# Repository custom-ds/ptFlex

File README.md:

# ptFlex
ptFlex tracker board starting with version 2.0 of the hardware, which is based on the improvements found in the ptSolar tracker. This repo supercedes the original ptFlex-firmware and ptFlex-Hardware repos from the version 1.0 hardware.

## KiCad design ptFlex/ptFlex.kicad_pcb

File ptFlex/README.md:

# ptFlex PCB
The ptFlex PCB has been designed for manufacture from JLC-PCB. The design rules checker have been tuned for their manufacturing tolerances.

The design and update process includes updating the Schematic in KiCad, updating the PCB layout based on the schematic changes in KiCad, then output the Gerber files and assembly documents for upload to JLC-PCB.

## Schematic Design
Any changes to the schematic should be completed first. When placing a part, be sure to update the Bill of Materials information by including the following two Fields in each component's properties.

* **Digikey** - The Digikey part number for ordering parts (critical for any parts that are not auto-assembled by JLC), and import for all other parts in the event that someone would want to hand-assemble their tracker.
* **LCSC** - The JLC-PCB Part number for automated assembly. This value is not populated for through-hole parts and the SA818V transmitter module (sources from Alibaba, etc)

### Schematic Outputs

#### Bill of Materials
Once complete with the Schematic, run the Tools &rarr; Generate Bill of Materials which places the BOM inside of the /Current folder.

#### PDF Output
Run File &rarr; Plot and output a PDF version of the schematics into the /Current folder. Be sure to rename this output to ```schematic.pdf``` in the output directory before plotting the PCB design.

## PCB Design
Inside of the Schematic editor, press F8 to update the PCB layout with any changes to the schematic. Adjust any layouts as necessary.

### Design Rule Checker
Once a layout has been laid out, run the DRC to check for problems with the board. The castelated edges normally throw a dozen or more errors. Also, there are some silkscreen issues with the coax connector at the top of the board. Any other errors should be investigated and resolved.

### Update the PCB Version
Update the Silkscreen text that indicates the version of the PCB.

### PCB Outputs

#### Drill Files
Run the Files &rarr; Fabrication Outputs &rarr; Gerber. From that screen, click the Generate Drill Files and output the .DRL files into the /Current folder. The format should be Excellon, and the units Millimeters.

#### Gerbers
Close out of the Drill files window, and click the File &rarr; Fabrication &rarr; Plot button to generate the set of Gerber files. These should also go into the /Current folder.

#### Position Files
Run File &rarr; Fabrication Outputs &rarr; Component Placement Files. Select CSV for the Format, then click Generate Position File.

In the /Current folder, find the newly created ptFlex-top-pos.csv file and open it with a text editor. The very first header line needs to be replaced with this line to align with JLC's naming scheme.

```
Designator,Val,Package,Mid X,Mid Y,Rotation,Layer
```

#### PDF Output
Run File &rarr; Plot and output a PDF version of the pcb into the /Current folder. Select options for Black & White, and to plot as a single .PDF document. Be sure to rename this output to ```pcb.pdf``` in the output directory.

## Ordering the PCBs
### Collecting the Output
Inside of the /Current directory, Zip up all of the files except the *.pdf and *.csv files. Name this .Zip file ptFlex-vX.X.X.zip, as appropriate for the board version.

## Upload to JLCPCB

Log in to your JLC-PCB account at [JLCPCB.com](https://www.jlcpcb.com/).

Upload the Gerbers to the site. For the ptFlex tracker, select the following options:
* Layers: 2
* PCB Qty: As desired
* Surface Finish: HASL (with lead)
* PCB Thickness: 1.6mm
* Castellated Holes: No
* PCB Assembly: As desired

### PCB Assembly
If PCB Assembly is desired:

* Assembly Side: Top Side 
* PCBA Qty: Select the quantity, up to the number of PCBs you selected in the first part

Select Next, then Next again.

Upload the following files:
* Add BOM: Upload the Bill of Materials.csv file.
* Add CPL: Upload the ptFlex-top-pos.csv file. Make sure that you modified the first header line as described above.

Process BOM & CPL. You will likely get an Error that certain Designators don't exist in the CPL file. That's just a warning that some parts that are located on the back of the board (SA818V and the Supercap) aren't found in the placement file. Click the Continue button if you receive this error.

Review the Bill of Materials and ensure that the part description matches the expected values. If certain parts aren't in-stock, you will either have to order them, or hand-place them once the semi-finished boards arrive.

Once the board layout appears with the components placed on it, you will need to review each of the placements of the parts. Many of the semiconductors will be rotated 90 of 180 degrees out of spec, and you will need to adjust them. The best optoin is to open the ptFlex-top-pos.csv file, and edit the rotation values inside of the file. By doing this, you will save the copy of rotations locally and re-ordering will be that much simpler and safer.

The column in question is the second-to-last field where most of the default values are 0.00000 or 180.00000.

For the ptFlex the following parts need to be tweaked in the X/Y position to fit the pads correctly:
* U1 (5V Regulator)
* J1 (Power Connector)

The following components need to be rotated:
* Q1-Q5 (transistors) - 180 degrees
* U2 (3.3V Regulator) - 90 degrees
* U3 (ATMega) - -90 degrees
* U4 (GPS) - -90 degrees
* U6 (BME280) - 90 degrees

## Create an Final Output Directory
Copy the entire contents of the /Current folder into a folder named for the PCB version. For example, /v2.0.0/ for safe keeping.

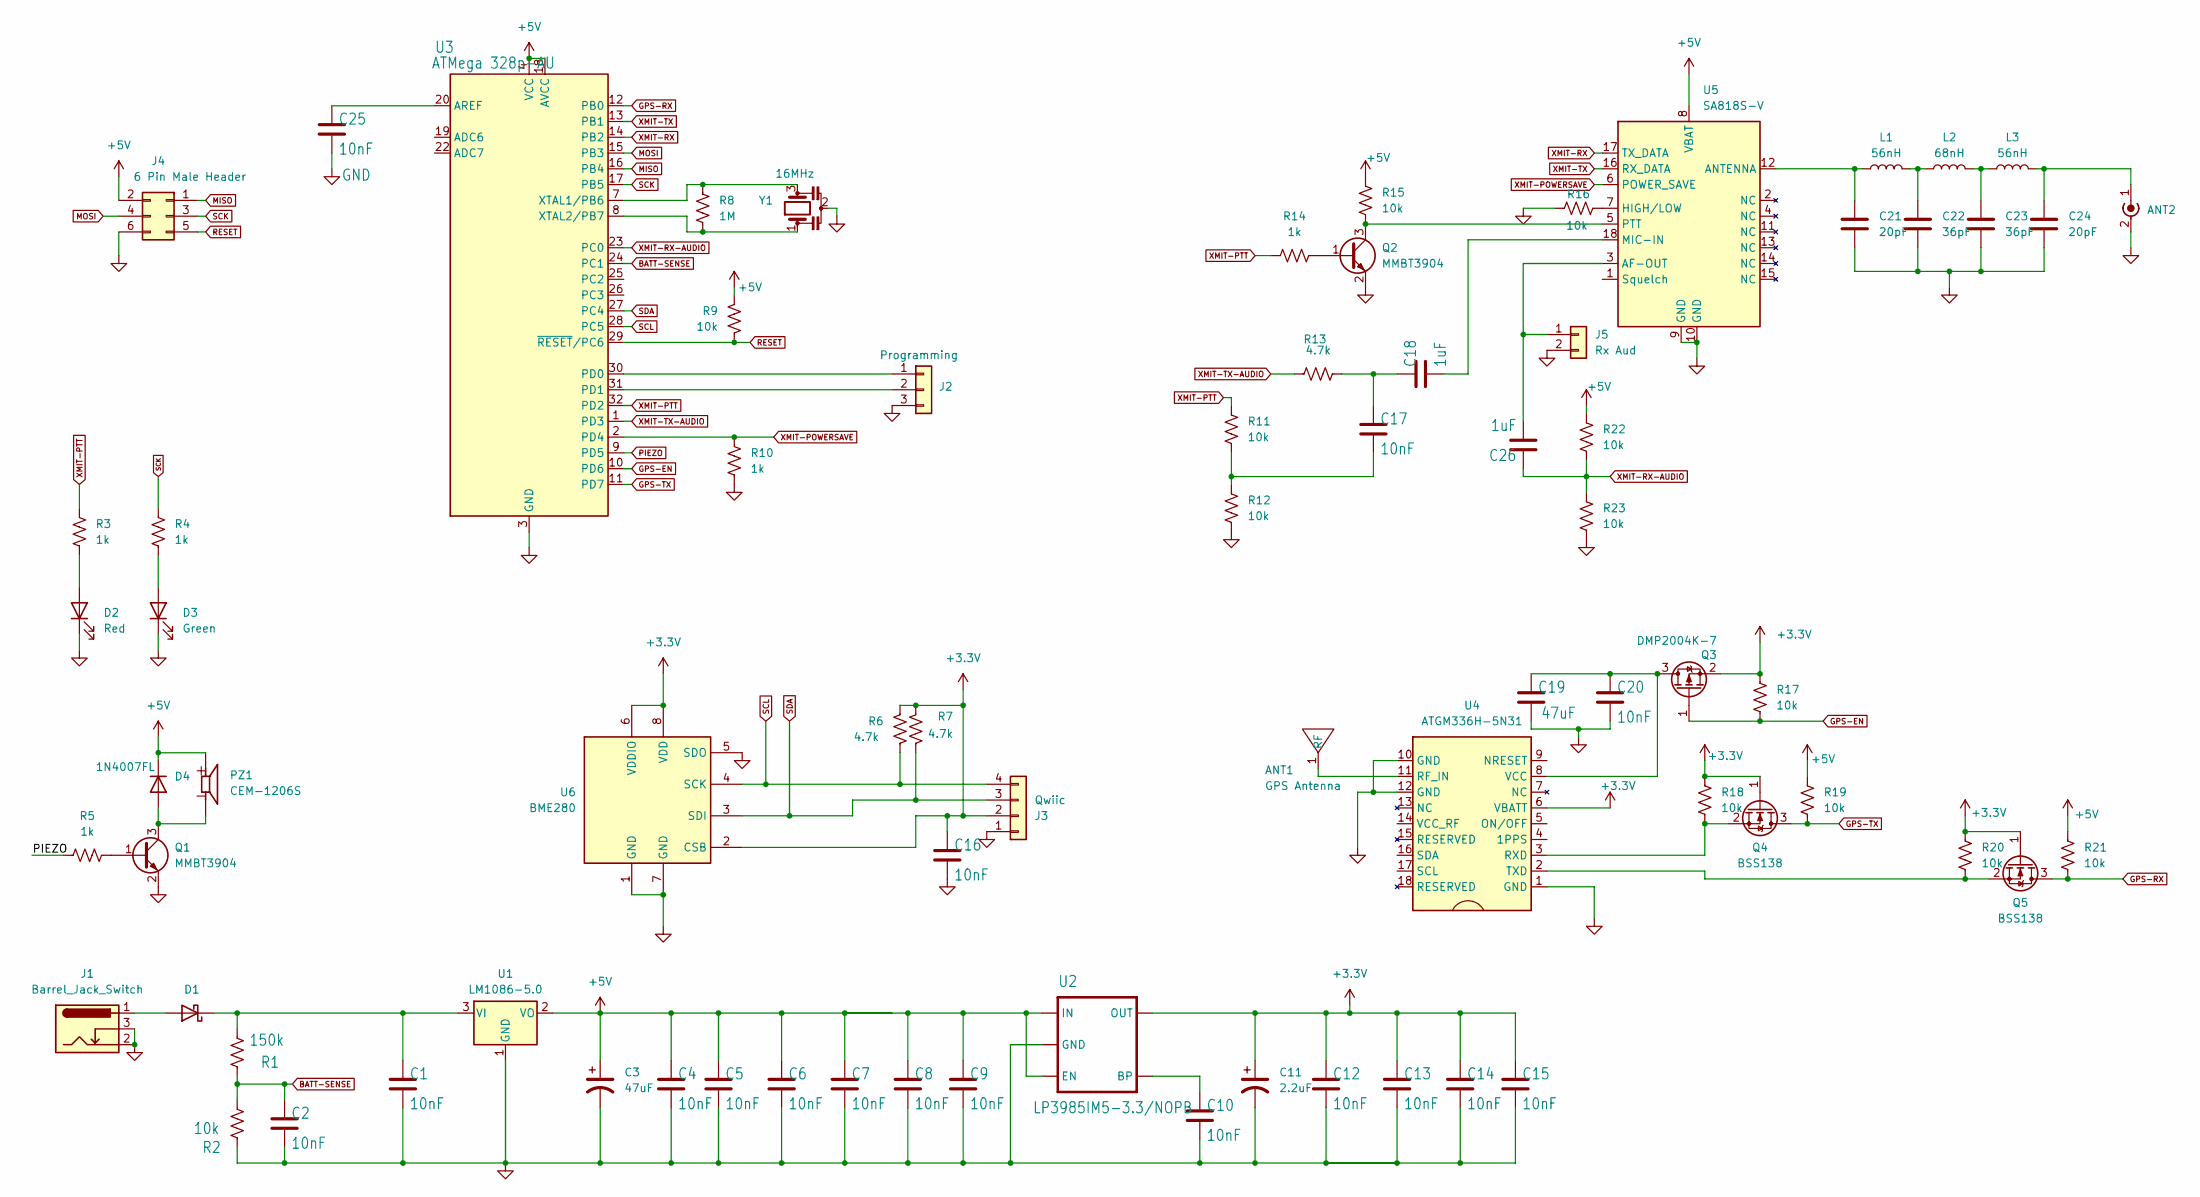
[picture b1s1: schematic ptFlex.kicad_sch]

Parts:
ANT1: GPS Antenna; Pulse ANT8010LL05R1575A Antenna; Digikey 553-ANT8010LL05R1575ACT-ND
ANT2: SMA Connector; SMA_Thru_Hole
C1, C2, C4, C5, C6, C7, C8, C9, C10, C12, C13, C14, C15, C16, C17, C20, C25: 10nF; C_0805_2012Metric; Digikey 399-1158-1-ND
C3, C19: 47uF; C_0805_2012Metric; Digikey 399-C0805C476M9PACTUCT-ND
C11: 2.2uF; C_0805_2012Metric; Digikey 445-1420-1-ND
C18, C26: 1uF; C_0805_2012Metric; Digikey 311-1886-1-ND
C21, C24: 20pF; C_0805_2012Metric; Digikey 712-1381-1-ND
C22, C23: 36pF; C_0805_2012Metric; Digikey 478-10473-1-ND
D1: CDBA340L-G Schottky; D_SMA; Digikey 641-1258-1-ND
D2: Red; D_0805_2012Metric; Digikey LTST-C171KRKT
D3: Green; D_0805_2012Metric; Digikey LTST-C171GKT
D4: 1N4007FL; D_SOD-123; Digikey 1655-1N4007FLCT-ND
J1: Barrel_Jack_Switch; BarrelJack_CLIFF_FC681465S_SMT_Horizontal; Digikey CP-002AHPJCT-ND
J2: Programming; PinHeader_1x03_P2.54mm_Vertical; Digikey 732-5316-ND
J3: Qwiic; JST_SH_SM04B-SRSS-TB_1x04-1MP_P1.00mm_Horizontal; Digikey 455-1804-1-ND
J4: 6 Pin Male Header; PinHeader_2x03_P2.54mm_Vertical; Digikey 732-5394-ND
J5: Rx Aud; PinHeader_1x02_P2.54mm_Vertical
L1, L3: 56nH; L_0805_2012Metric; Digikey 535-11570-1-ND
L2: 68nH; L_0805_2012Metric; Digikey 535-11572-1-ND
PZ1: CEM-1206S; CUI_CEM-1206S
Q1, Q2: MMBT3904; SOT-23; Digikey MMBT3904TPMSCT-ND
Q3: DMP2004K-7; SOT-23; Digikey DMP2004KDICT-ND
Q4, Q5: BSS138; SOT-23; Digikey BSS138TR-ND
R1: 150k; R_0805_2012Metric; Digikey 311-150KCRCT-ND
R2, R9, R11, R12, R15, R16, R17, R18, R19, R20, R21, R22, R23: 10k; R_0805_2012Metric; Digikey 13-RT0805FRD0710KLCT-ND
R3, R4, R5, R10, R14: 1k; R_0805_2012Metric; Digikey 311-1.0KARCT-ND
R6, R7, R13: 4.7k; R_0805_2012Metric; Digikey 311-4.7KARCT-ND
R8: 1M; R_0805_2012Metric; Digikey 311-1.0MARCT-ND
U1: LM1086-5.0; TO-263-3_TabPin2; Digikey LM1086ISX-5.0/NOPBCT-ND
U2: LP3985IM5-3.3/NOPB; SOT-23-5; Digikey LP3985IM5-3.3/NOPBCT-ND
U3: ATMega 328p-AU; TQFP-32_7x7mm_P0.8mm; Digikey ATMEGA328P-AU-ND
U4: ATGM336H-5N31; Digikey ALIEXPRESS
U5: SA818S-V; DRA818 SA818; Digikey ALIEXPRESS
U6: BME280; Bosch_LGA-8_2.5x2.5mm_P0.65mm_ClockwisePinNumbering; Digikey 828-1063-1-ND
Y1: 16MHz; Resonator_SMD_Murata_CSTxExxV-3Pin_3.0x1.1mm; Digikey 490-17948-2-ND

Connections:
+3.3V: C11.1, C12.1, C13.1, C14.1, C15.1, C16.1, J3.2, Q3.2 (S), Q4.1 (G), Q5.1 (G), R6.1, R7.1, R17.1, R18.2, R20.2, U2.5 (OUT), U4.6 (VBATT), U6.2 (CSB), U6.6 (VDDIO), U6.8 (VDD)
+5V: C3.1, C4.1, C5.1, C6.1, C7.1, C8.1, C9.1, D4.1 (K), J4.2, PZ1.P, R9.1, R15.2, R19.2, R21.2, R22.2, U1.2 (VO), U2.1 (IN), U2.3 (EN), U3.4 (VCC), U3.6 (VCC), U3.18 (AVCC), U5.8 (VBAT)
BATT-SENSE: C2.1, R1.1, R2.2, U3.24 (PC1)
GND: ANT2.2 (Ext), C1.2, C2.2, C3.2, C4.2, C5.2, C6.2, C7.2, C8.2, C9.2, C10.2, C11.2, C12.2, C13.2, C14.2, C15.2, C16.2, C19.2, C20.2, C21.1, C22.1, C23.1, C24.1, C25.2, D2.1 (K), D3.1 (K), J1.2, J1.3, J2.3, J3.1, J4.6, J5.2, Q1.2 (E), Q2.2 (E), R2.1, R10.1, R12.1, R16.1, R23.1, U1.1 (GND), U2.2 (GND), U3.3 (GND), U3.5 (GND), U3.21 (GND), U4.1 (GND), U4.10 (GND), U4.12 (GND), U5.9 (GND), U5.10 (GND), U6.1 (GND), U6.5 (SDO), U6.7 (GND), Y1.2
GPS-EN: Q3.1 (G), R17.2, U3.10 (PD6)
GPS-RX: Q5.3 (D), R21.1, U3.12 (PB0)
GPS-TX: Q4.3 (D), R19.1, U3.11 (PD7)
MISO: J4.1, U3.16 (PB4)
MOSI: J4.4, U3.15 (PB3)
unnamed: ANT1.1 (RF), U4.11 (RF_IN)
unnamed: ANT2.1 (In), C24.2, L3.2
unnamed: C17.1, C18.1, R13.2
unnamed: C17.2, R11.1, R12.2
unnamed: C22.2, L1.2, L2.1
unnamed: C23.2, L2.2, L3.1
unnamed: D1.2 (A), J1.1
unnamed: C1.1, D1.1 (K), R1.2, U1.3 (VI)
unnamed: D2.2 (A), R3.2
unnamed: D3.2 (A), R4.2
unnamed: D4.2 (A), PZ1.N, Q1.3 (C)
unnamed: J2.1, U3.30 (PD0)
unnamed: J2.2, U3.31 (PD1)
unnamed: C26.2, J5.1, U5.3 (AF-OUT)
unnamed: Q1.1 (B), R5.1
unnamed: Q2.1 (B), R14.2
unnamed: Q2.3 (C), R15.1, U5.5 (PTT)
unnamed: C19.1, C20.1, Q3.3 (D), U4.8 (VCC)
unnamed: Q4.2 (S), R18.1, U4.3 (RXD)
unnamed: Q5.2 (S), R20.1, U4.2 (TXD)
unnamed: C10.1, U2.4 (BP)
unnamed: C25.1, U3.20 (AREF)
unnamed: R8.1, U3.7 (XTAL1/PB6), Y1.3
unnamed: R8.2, U3.8 (XTAL2/PB7), Y1.1
unnamed: C21.2, L1.1, U5.12 (ANTENNA)
unnamed: R16.2, U5.7 (HIGH/LOW)
unnamed: C18.2, U5.18 (MIC-IN)
PIEZO: R5.2, U3.9 (PD5)
RESET: J4.5, R9.2, U3.29 (~RESET/PC6)
SCK: J4.3, R4.1, U3.17 (PB5)
SCL: J3.4, R6.2, U3.28 (PC5), U6.4 (SCK)
SDA: J3.3, R7.2, U3.27 (PC4), U6.3 (SDI)
XMIT-POWERSAVE: R10.2, U3.2 (PD4), U5.6 (POWER_SAVE)
XMIT-PTT: R3.1, R11.2, R14.1, U3.32 (PD2)
XMIT-RX: U3.14 (PB2), U5.17 (TX_DATA)
XMIT-RX-AUDIO: C26.1, R22.1, R23.2, U3.23 (PC0)
XMIT-TX: U3.13 (PB1), U5.16 (RX_DATA)
XMIT-TX-AUDIO: R13.1, U3.1 (PD3)

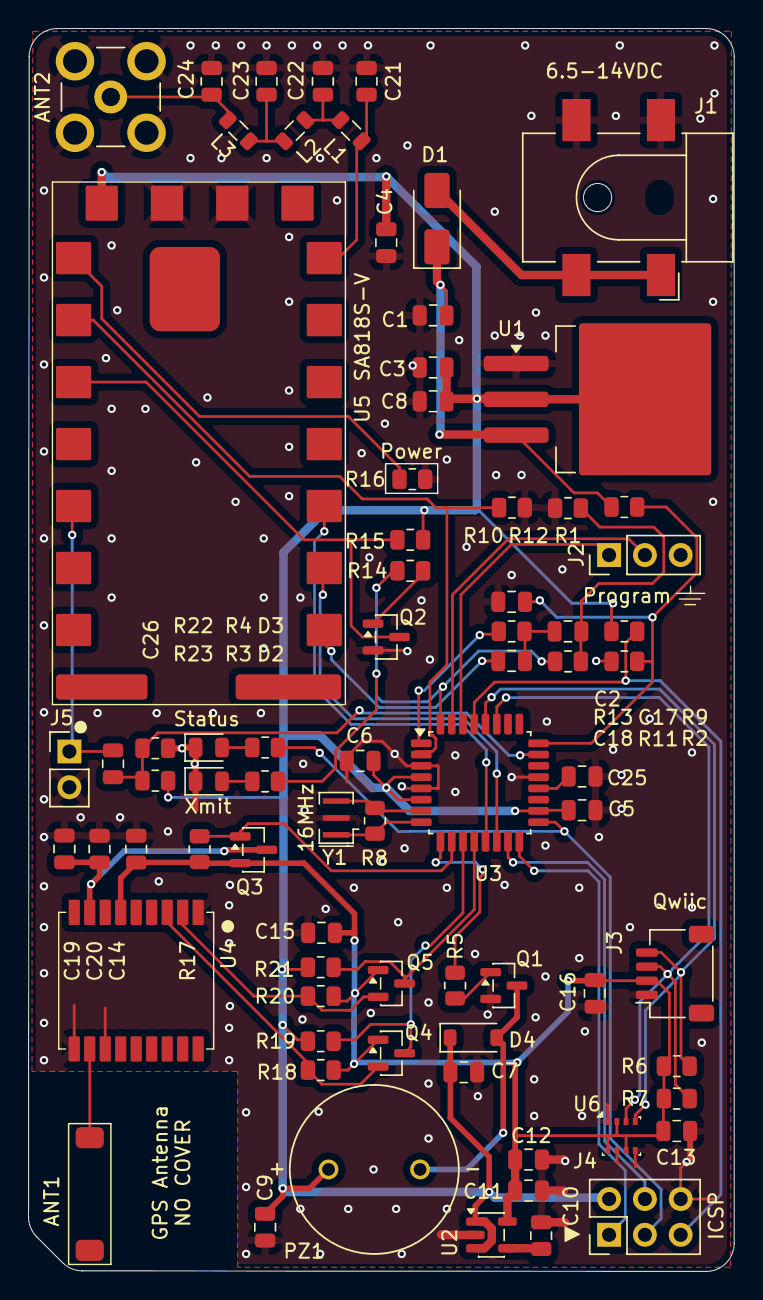
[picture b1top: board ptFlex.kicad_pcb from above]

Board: 2 copper layers, 50.1 x 88.2 mm, 76 parts (0 on the bottom side), 47 nets.

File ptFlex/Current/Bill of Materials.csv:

"Reference","Value","Datasheet","Footprint","Qty","DNP","Digikey","LCSC"
"ANT1","GPS Antenna","","Custom DS:Pulse ANT8010LL05R1575A Antenna","1","","553-ANT8010LL05R1575ACT-ND","C3284202"
"ANT2","SMA Connector","~","Custom DS:SMA_Thru_Hole","1","","",""
"C1,C2,C4,C5,C6,C7,C8,C9,C10,C12,C13,C14,C15,C16,C17,C20,C25","10nF","~","Capacitor_SMD:C_0805_2012Metric","17","","399-1158-1-ND","C83170"
"C3,C19","47uF","~","Capacitor_SMD:C_0805_2012Metric","2","","399-C0805C476M9PACTUCT-ND","C16780"
"C11","2.2uF","~","Capacitor_SMD:C_0805_2012Metric","1","","445-1420-1-ND","C107128"
"C18","1uF","~","Capacitor_SMD:C_0805_2012Metric","1","","311-1886-1-ND","C28323"
"C21,C24","20pF","~","Capacitor_SMD:C_0805_2012Metric","2","","712-1381-1-ND","C105173"
"C22,C23","36pF","~","Capacitor_SMD:C_0805_2012Metric","2","","478-10473-1-ND","C541518"
"D1","CDBA340L-G Schottky","~","Diode_SMD:D_SMA","1","","641-1258-1-ND","C22364900"
"D2","Red","~","Diode_SMD:D_0805_2012Metric","1","","LTST-C171KRKT","C2295"
"D3","Green","~","Diode_SMD:D_0805_2012Metric","1","","LTST-C171GKT","C2297 "
"D4","1N4007FL","","Diode_SMD:D_SOD-123","1","","1655-1N4007FLCT-ND","C7528871"
"J1","Barrel_Jack_Switch","~","Connector_BarrelJack:BarrelJack_CLIFF_FC681465S_SMT_Horizontal","1","","CP-002AHPJCT-ND ","C22434687"
"J2","Programming","~","Connector_PinHeader_2.54mm:PinHeader_1x03_P2.54mm_Vertical","1","","732-5316-ND",""
"J3","Qwiic","~","Connector_JST:JST_SH_SM04B-SRSS-TB_1x04-1MP_P1.00mm_Horizontal","1","","455-1804-1-ND","C160404"
"J4","6 Pin Male Header","~","Connector_PinHeader_2.54mm:PinHeader_2x03_P2.54mm_Vertical","1","","732-5394-ND",""
"L1,L3","56nH","~","Inductor_SMD:L_0805_2012Metric","2","","535-11570-1-ND","C98996"
"L2","68nH","~","Inductor_SMD:L_0805_2012Metric","1","","535-11572-1-ND","C75652"
"PZ1","CEM-1206S","","Custom DS:CUI_CEM-1206S","1","","",""
"Q1,Q2","MMBT3904","https://www.onsemi.com/pdf/datasheet/pzt3904-d.pdf","Package_TO_SOT_SMD:SOT-23","2","","MMBT3904TPMSCT-ND","C81464"
"Q3","DMP2004K-7","","Package_TO_SOT_SMD:SOT-23","1","","DMP2004KDICT-ND","C332297"
"Q4,Q5","BSS138","https://www.onsemi.com/pub/Collateral/BSS138-D.PDF","Package_TO_SOT_SMD:SOT-23","2","","BSS138TR-ND","C40912 "
"R1","150k","~","Resistor_SMD:R_0805_2012Metric","1","","311-150KCRCT-ND","C114558"
"R2,R9,R11,R12,R15,R16,R17,R18,R19,R20,R21","10k","~","Resistor_SMD:R_0805_2012Metric","11","","13-RT0805FRD0710KLCT-ND","C100047"
"R3,R4,R5,R10,R14","1k","~","Resistor_SMD:R_0805_2012Metric","5","","311-1.0KARCT-ND","C95781"
"R6,R7,R13","4.7k","~","Resistor_SMD:R_0805_2012Metric","3","","311-4.7KARCT-ND","C60816"
"R8","1M","~","Resistor_SMD:R_0805_2012Metric","1","","311-1.0MARCT-ND","C107700"
"U1","LM1086-5.0","","Package_TO_SOT_SMD:TO-263-3_TabPin2","1","","LM1086ISX-5.0/NOPBCT-ND","C5145331"
"U2","LP3985IM5-3.3/NOPB","https://www.ti.com/lit/ds/symlink/lp3985.pdf?HQS=dis-dk-null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","Package_TO_SOT_SMD:SOT-23-5","1","","LP3985IM5-3.3/NOPBCT-ND","C108877"
"U3","ATMega 328p-AU","https://ww1.microchip.com/downloads/en/DeviceDoc/Atmel-7810-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","Package_QFP:TQFP-32_7x7mm_P0.8mm","1","","ATMEGA328P-AU-ND","C14877"
"U4","ATGM336H-5N31","https://www.tinytronics.nl/product_files/002176_ATGM336H.pdf","Custom DS:ATGM336H-5N31","1","","ALIEXPRESS","C90770"
"U5","SA818S-V","","Custom DS:DRA818 SA818","1","","ALIEXPRESS",""
"U6","BME280","https://www.bosch-sensortec.com/media/boschsensortec/downloa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","Package_LGA:Bosch_LGA-8_2.5x2.5mm_P0.65mm_ClockwisePinNumbering","1","","828-1063-1-ND","C92489"
"Y1","16MHz","~","Crystal:Resonator_SMD_Murata_CSTxExxV-3Pin_3.0x1.1mm","1","","490-17948-2-ND","C341521"

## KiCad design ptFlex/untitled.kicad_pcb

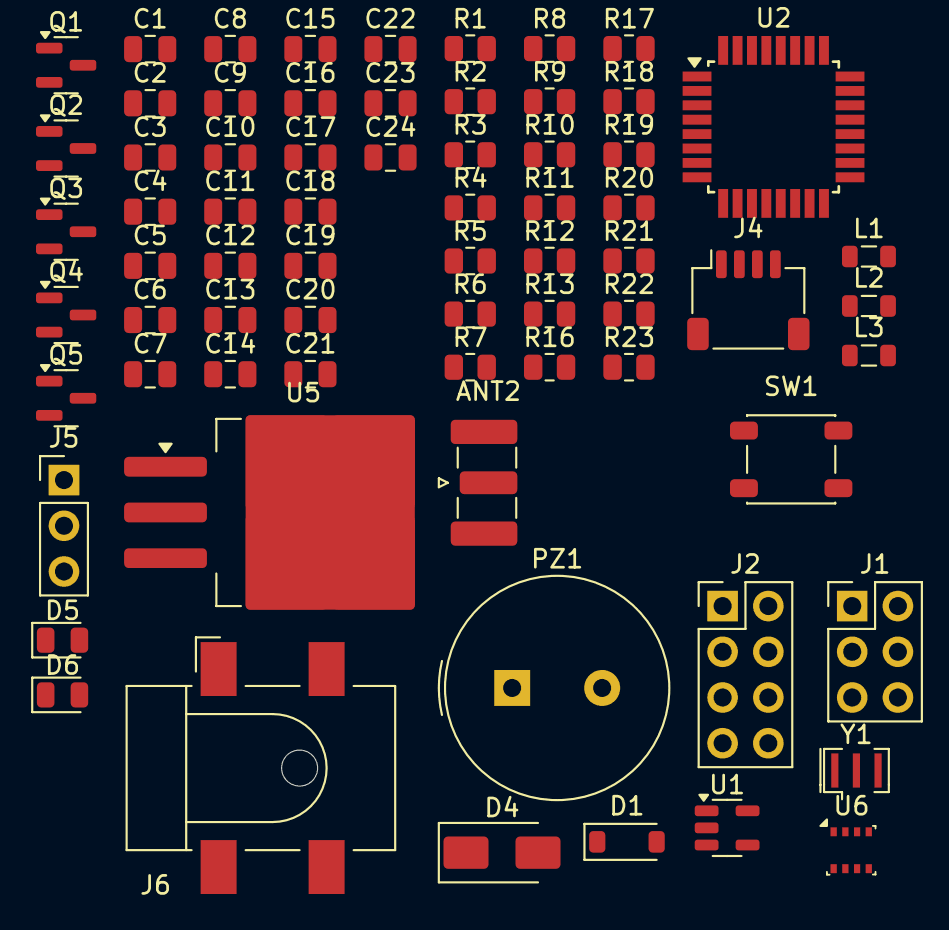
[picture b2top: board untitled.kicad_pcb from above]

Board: 2 copper layers, 70 parts (0 on the bottom side), 41 nets, no tracks yet.

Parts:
ANT2: SMA Edge Mount (Optional); SMA_Samtec_SMA-J-P-H-ST-EM1_EdgeMount
C1, C2, C3, C4, C5, C6, C7, C9, C10, C11, C13, C15, C20, C22, C23, C24: 10nF; C_0805_2012Metric
C8, C21: 2.2uF; C_0805_2012Metric
C12: 47uF; C_0805_2012Metric
C14: 1uF; C_0805_2012Metric
C16, C19: 20pF; C_0805_2012Metric
C17, C18: 36pF; C_0805_2012Metric
D1: 1N4007FL; D_SOD-123
D4: CDBA340L-G Schottky; D_SMA
D5: Red; D_0805_2012Metric
D6: Green; D_0805_2012Metric
J1: 6 Pin Male Header; PinHeader_2x03_P2.54mm_Vertical
J2: 8 Pin Male Header; PinHeader_2x04_P2.54mm_Vertical
J4: Qwiic; JST_SH_SM04B-SRSS-TB_1x04-1MP_P1.00mm_Horizontal
J5: 3 Pin Male Header; PinHeader_1x03_P2.54mm_Vertical
J6: Barrel_Jack_Switch; BarrelJack_CLIFF_FC681465S_SMT_Horizontal
L1, L3: 56nH; L_0805_2012Metric
L2: 68nH; L_0805_2012Metric
PZ1: Piezo Buzzer; Buzzer_TDK_PS1240P02BT_D12.2mm_H6.5mm
Q1, Q2: BSS138; SOT-23
Q3, Q4: MMBT3904; SOT-23
Q5: DMP2004K-7; SOT-23
R1, R4, R5, R17, R22: 1k; R_0805_2012Metric
R2: 100k; R_0805_2012Metric
R3: 22k; R_0805_2012Metric
R6: 1M; R_0805_2012Metric
R7, R10, R11, R12, R13, R18, R19, R20, R21, R23: 10k; R_0805_2012Metric
R8, R9, R16: 4.7k; R_0805_2012Metric
SW1: Reset Switch; SW_SPST_PTS647_Sx38
U1: LP3985IM5-3.3/NOPB; SOT-23-5
U2: ATMega 328p-AU; TQFP-32_7x7mm_P0.8mm
U5: LM1086-5.0; TO-263-3_TabPin2
U6: BME280; Bosch_LGA-8_2.5x2.5mm_P0.65mm_ClockwisePinNumbering
Y1: 8MHz; Resonator_SMD_Murata_CSTxExxV-3Pin_3.0x1.1mm

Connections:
+3.3V: C8.1, C9.1, C10.1, C11.1, C12.1, C24.1, J2.2, J4.2, Q1.1 (G), Q2.1 (G), Q5.2 (S), R7.1, R8.1, R9.1, R10.2, R12.2, R23.1, U1.5 (OUT), U2.4 (VCC), U2.6 (VCC), U2.18 (AVCC), U6.2 (CSB), U6.6 (VDDIO), U6.8 (VDD)
+BATT: C3.1, C4.1, C5.1, C6.1, C21.1, C22.1, C23.1, D1.1 (K), D4.1 (K), J1.2, PZ1.1, R2.2, R11.2, R13.2, R18.2, U1.1 (IN), U1.3 (EN), U5.2 (VO)
/BATT-SENSE: C2.1, R2.1, R3.2, U2.24 (PC1)
/DIG-PTT: J2.7, R4.1, R17.1, R20.2, U2.32 (PD2)
/GPS-EN: Q5.1 (G), R23.2, U2.10 (PD6)
/MISO: J1.1, U2.16 (PB4)
/MOSI: J1.4, U2.15 (PB3)
/RESET: J1.5, R7.2, U2.29 (~RESET/PC6)
/SCK: J1.3, R5.1, U2.17 (PB5)
/SCL: J2.4, R8.2, U2.28 (PC5)
/SDA: J2.6, R9.2, U2.27 (PC4)
GND: ANT2.2 (Ext), C1.2, C2.2, C3.2, C4.2, C5.2, C6.2, C7.2, C8.2, C9.2, C10.2, C11.2, C12.2, C13.2, C16.1, C17.1, C18.1, C19.1, C20.2, C21.2, C22.2, C23.2, C24.2, D5.1 (K), D6.1 (K), J1.6, J2.5, J4.1, J5.3, J6.2, J6.3, Q3.2 (E), Q4.2 (E), R3.1, R19.1, R21.1, R22.1, SW1.2 (B), U1.2 (GND), U2.3 (GND), U2.5 (GND), U2.21 (GND), U5.1 (GND), U6.1 (GND), U6.5 (SDO), U6.7 (GND), Y1.2
unnamed: ANT2.1 (In), C19.2, L3.2
unnamed: C14.1, C15.1, R16.2
unnamed: C15.2, R20.1, R21.2
unnamed: C17.2, L1.2, L2.1
unnamed: C18.2, L2.2, L3.1
unnamed: D1.2 (A), PZ1.2, Q3.3 (C)
unnamed: D5.2 (A), R4.2
unnamed: D6.2 (A), R5.2
unnamed: J2.1, U2.30 (PD0)
unnamed: J2.3, U2.31 (PD1)
unnamed: J2.8, U2.9 (PD5)
unnamed: J4.3, U6.3 (SDI)
unnamed: J4.4, U6.4 (SCK)
unnamed: Q1.3 (D), R11.1
unnamed: Q1.2 (S), R10.1
unnamed: Q2.3 (D), R13.1
unnamed: Q2.2 (S), R12.1
unnamed: Q3.1 (B), R1.1
unnamed: Q4.1 (B), R17.2
unnamed: Q4.3 (C), R18.1
unnamed: C20.1, Q5.3 (D)
unnamed: C7.1, U1.4 (BP)
unnamed: C13.1, U2.20 (AREF)
unnamed: R16.1, U2.1 (PD3)
unnamed: R22.2, U2.2 (PD4)
unnamed: R6.1, U2.7 (XTAL1/PB6), Y1.3
unnamed: R6.2, U2.8 (XTAL2/PB7), Y1.1
unnamed: C16.2, L1.1
unnamed: C1.1, J6.1, U5.3 (VI)

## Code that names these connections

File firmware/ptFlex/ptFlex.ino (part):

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#include "SparkFunBME280.h"
#include <Wire.h>

//PD0 is Serial Port RX
//PD1 is Serial Port TX
#define PIN_PTT_OUT 2     //PD2
#define PIN_AUDIO_OUT 3   //PD3   - APRS Packet Audio
#define PIN_DRA_EN 4      //PD4
#define PIN_AUDIO 5       //PD5   - Audio Annunciation
#define PIN_GPS_EN 6      //PD6
#define PIN_GPS_TX 7      //PD7

#define PIN_GPS_RX 8      //PB0
#define PIN_DRA_TX 9      //PB1
#define PIN_DRA_RX 10     //PB2
//PB3 is MOSI
//PB4 is MISO
#define PIN_LED 13        //PB5

//Analog Pins
#define PIN_AUDIO_IN A0   //PC0
#define PIN_ANALOG_BATTERY A1   //PC1
//PC2 is not used
//PC3 is not used
//PC4 is SDA
//PC5 is SCL
//PC6 is reset and not available


#define DELAY_MS_BETWEEN_XMITS 1250   //How many MS to delay between subsequent packets (as in between GPGGA and GPRMC strings
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      break;
  }
  
  OCR2B = Aprs.getDACValue(highByte(iTonePhase));   //analogWrite to PIN PD3, directly using the OCR register

  iRateGen--;
  if (iRateGen == 0) {
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
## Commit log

2025-06-15 Initial transfer of ptSolar to ptFlex starter files.
2025-06-21 Schematic mostly revised for v2.0
2025-06-21 PCB nearing final
2025-06-22 Back filed old versions of PCB from the ptFlex-hardware project into this repo. Shrunk the PCB down by 5mm.
2025-06-22 Swapped out Piezo symbol. Minor tweaks
2025-06-22 Renumbered all parts.
2025-06-24 Finalized version 2.0.0 of the PCB to bring it in sync with the ptSolar design.
2025-07-11 Migrated firmware from ptSolar to ptFlex. Adjusting for new defaults, 16MHz clock speed, and voltage sense divider change.
2025-07-12 Updated to firmware 1.5.0. This includes a few minor fixes, and an update to configuration version PT0101. Backwards support for alternate GPS and transmitters has been removed.
2025-07-19 Board redesigned to 2.0.1 to fix missing SDA/SCL pins to uC. Shrunk board slightly. Fixed SMA center hole being too small.
2025-07-21 Version 1.5.1 syncs up the libraries between ptFlex and ptSolar.
2025-07-29 Firmware 1.5.2. Added feature to adjust path when transmitting on ISS frequency.
2025-07-29 Adjusting voltage divider resistor precision.
2025-08-22 Updating to PCB 2.0.1 to fix missing I2C wires.
2025-09-26 Updates synced for 1.6
2025-09-27 Adjusting for cold-weather operation.
2025-09-27 General clean up
2025-09-27 Adjusting gitignore
2026-04-12 Finalizing PCB v2.0.2. Including some minor tweaks to the firmware as well.
2026-04-20 Adjusting to better defaults in the firmware's configuration.
2026-04-21 Updated to firmware 1.6.1. Simplified test tools to function with ptConfigurator.
2026-05-18 Updated BOM parts
2026-05-18 Added logic to handle invalid gps fix.
2026-05-31 Limiting GPS debug noise
2026-05-31 Fix for GPS Delay being out of order in config strings
2026-06-09 Better debug output when handling GPS delays.
2026-06-09 Replaced missing files

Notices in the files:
firmware/ptFlex/ptFlex.ino:
Copyright 2011-2026 - Zack Clobes (W0ZC), Custom Digital Services, LLC
This program is free software: you can redistribute it and/or modify it under the terms of the GNU General Public License as published by
the Free Software Foundation, either version 3 of the License, or (at your option) any later version.
